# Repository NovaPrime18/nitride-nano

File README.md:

# nitride-nano

**Pocket-sized GaN buck/boost converter with USB-C PD input**

<table><tr>
<td></td>
<td></td>
</tr></table>

---

## Overview

Nitride-nano is an open-source, high-power-density buck/boost converter crammed into the smallest footprint possible. It targets the same use case as the [Miniware MDP-XP](https://www.miniware.com.cn/product/mdp-xp-digital-power-supply/)  a portable, wide-range programmable power supply. With a focus on **higher power density and a wider voltage range** rather than output ripple performance.

Built around EPC GaN FETs switching at up to 1 MHz and an LT8390A-based controller topology, it accepts either USB-C Power Delivery or high-voltage DC input and delivers up to 240 W from an XT90 output connector.

---

## Specifications

| Parameter | Value |
|---|---|
| Input voltage | 12 – 48 V |
| Output voltage | 0 – 60 V |
| Input / Output current | 20 A |
| Max output power | 240 W |
| Switching frequency | 1 MHz  |
| Topology | Non-inverting buck/boost |
| Input | XT90 / USB-C |
| Output | XT90 |
---

## USB-C Power Delivery

Nitride-nano negotiates full USB-C PD on the input side:

- **Fixed PDO** — standard 5/9/12/15/20 V profiles
- **PPS** — 5–21 V programmable (50 mV steps)
- **AVS / EPR** — 15–48 V extended power range

---

## Hardware

| Component | Part |
|---|---|
| MCU | STM32G474CEUx |
| Power stage FETs | EPC2367 (eGaN) |
| Controller | LT8390A / EVAL-LT8390A-AZ topology |
| Power monitor | INA228 (I²C, 16-bit) |
| Display | SSD1306 0.96″ OLED |
| UI | 3-button interface |

---

## Firmware

- STM32G474 HAL / bare-metal Rust
- SSD1306 OLED UI with 3-button navigation
- USB-C PD stack (Fixed / PPS / AVS negotiation) over I²C
- **Auto-tracking PD** — derives the input rail from the requested output voltage so the LT8390A stays in a clean buck or boost region instead of its lossier 4-switch band
- INA228 input/output power monitoring and real-time efficiency readout

---

## Thermal Sim
<table><tr>
<td></td>
<td></td>
</tr></table>

Simulated with Freecad, the enclosure reaches about 38 Degrees C (with a fan) when there's 10W of losses directly going into the heatsink from the GaNFETs. Real world performance is likely better, due to not all 10W leaving the Fets through the top.

---

## Testing — Revision 1 (1 MHz)

Bench results from Revision 1 hardware, measured at the operating points below.

| # | Input | Output | Efficiency |
|---|---|---|---|
| 1 | 25 V, 7 A — 174.2 W in | 36.6 V, 4.48 A — 164 W out | 94.1 % |
| 2 | 40 V, 3.61 A — 144.3 W in | 37.1 V, 3.48 A — 129.1 W out | 89.5 % |
| 3 | 13 V, 9.28 A — 120.6 W in | 36.5 V, 3 A — 109.1 W out | 90.5 % |

**Equipment:** Riden RD6024 bench supply (input) · EA-EL 3160-60 electronic load (output)

**Thermals:** the inductor core ran hottest at ~90 °C — by far the lossiest component on the board. The GaN FETs barely got above 60 °C.

---

## Testing — Revision 2 (2.2 µH, 1 MHz)

Bench results from Revision 2 hardware with the 2.2 µH Coilcraft XAL1010-222MED
inductor at 1 MHz switching. Efficiency is `Pout / Pin`.

### USB-C input

| # | Input | Output | Efficiency |
|---|---|---|---|
| 1 | 28 V, 3.957 A — 110.8 W in | 12.4 V, 8.04 A — 99.7 W out | 90.0 % |
| 2 | 36 V, 2.288 A — 82.4 W in | 12.4 V, 6.09 A — 75.5 W out | 91.7 % |
| 3 | 20 V, 4.75 A — 95.0 W in | 6.4 V, 12.92 A — 82.7 W out | 87.0 % |

### XT90 input

| # | Input | Output | Efficiency |
|---|---|---|---|
| 1 | 16 V, 10.54 A — 168.6 W in | 52 V, 2.97 A — 154.4 W out | 91.6 % |
| 2 | 13.81 V, 12.71 A — 175.5 W in | 38.6 V, 4 A — 154.4 W out | 88.0 % |
| 3 | 16 V, 14.13 A — 226.1 W in | 51.7 V, 4 A — 206.8 W out | 91.5 % |
| 4 | 16 V, 14.86 A — 237.8 W in | 51.8 V, 4.2 A — 217.6 W out | 91.5 % |
| 5 | 14 V, 17.2 A — 240.8 W in | 51.7 V, 4.2 A — 217.1 W out | 90.2 % |
| 6 | 24 V, 9.72 A — 233.3 W in | 52 V, 4.18 A — 217.4 W out | 93.2 % |
| 7 | 36 V, 6.42 A — 231.1 W in | 52.4 V, 4.18 A — 219.0 W out | 94.8 % |

**Peak efficiency:** 94.8 % at 36 V in → 52.4 V, 4.18 A (219.0 W out). The
highest input-power point was 240.8 W (14 V, 17.2 A) at 90.2 %; peak output
power was 219.0 W, up from 164 W on Revision 1.

---

## Acknowledgements / Based On

- [**PD240W** by theohg](https://github.com/theohg/PD240W) — USB-C PD input stage reference
- [**EVAL-LT8390A-AZ** by Analog Devices](https://www.analog.com/en/resources/evaluation-hardware-and-software/evaluation-boards-kits/eval-lt8390a-az.html) — buck/boost power stage reference

---

## License

Hardware design files are licensed under the **CERN Open Hardware Licence Version 2 – Strongly Reciprocal (CERN-OHL-S v2.0)**.

See [`LICENSE`](./LICENSE) for the full text, or visit [ohwr.org/cern_ohl_s_v2](https://ohwr.org/cern_ohl_s_v2.txt).

> In short: you are free to use, study, modify, and distribute this design, provided that any derivatives are released under the same licence and source files are made available.

---

## Status

> 🚧 Work in progress — Revision 1 and Revision 2 built and power-tested (results above).

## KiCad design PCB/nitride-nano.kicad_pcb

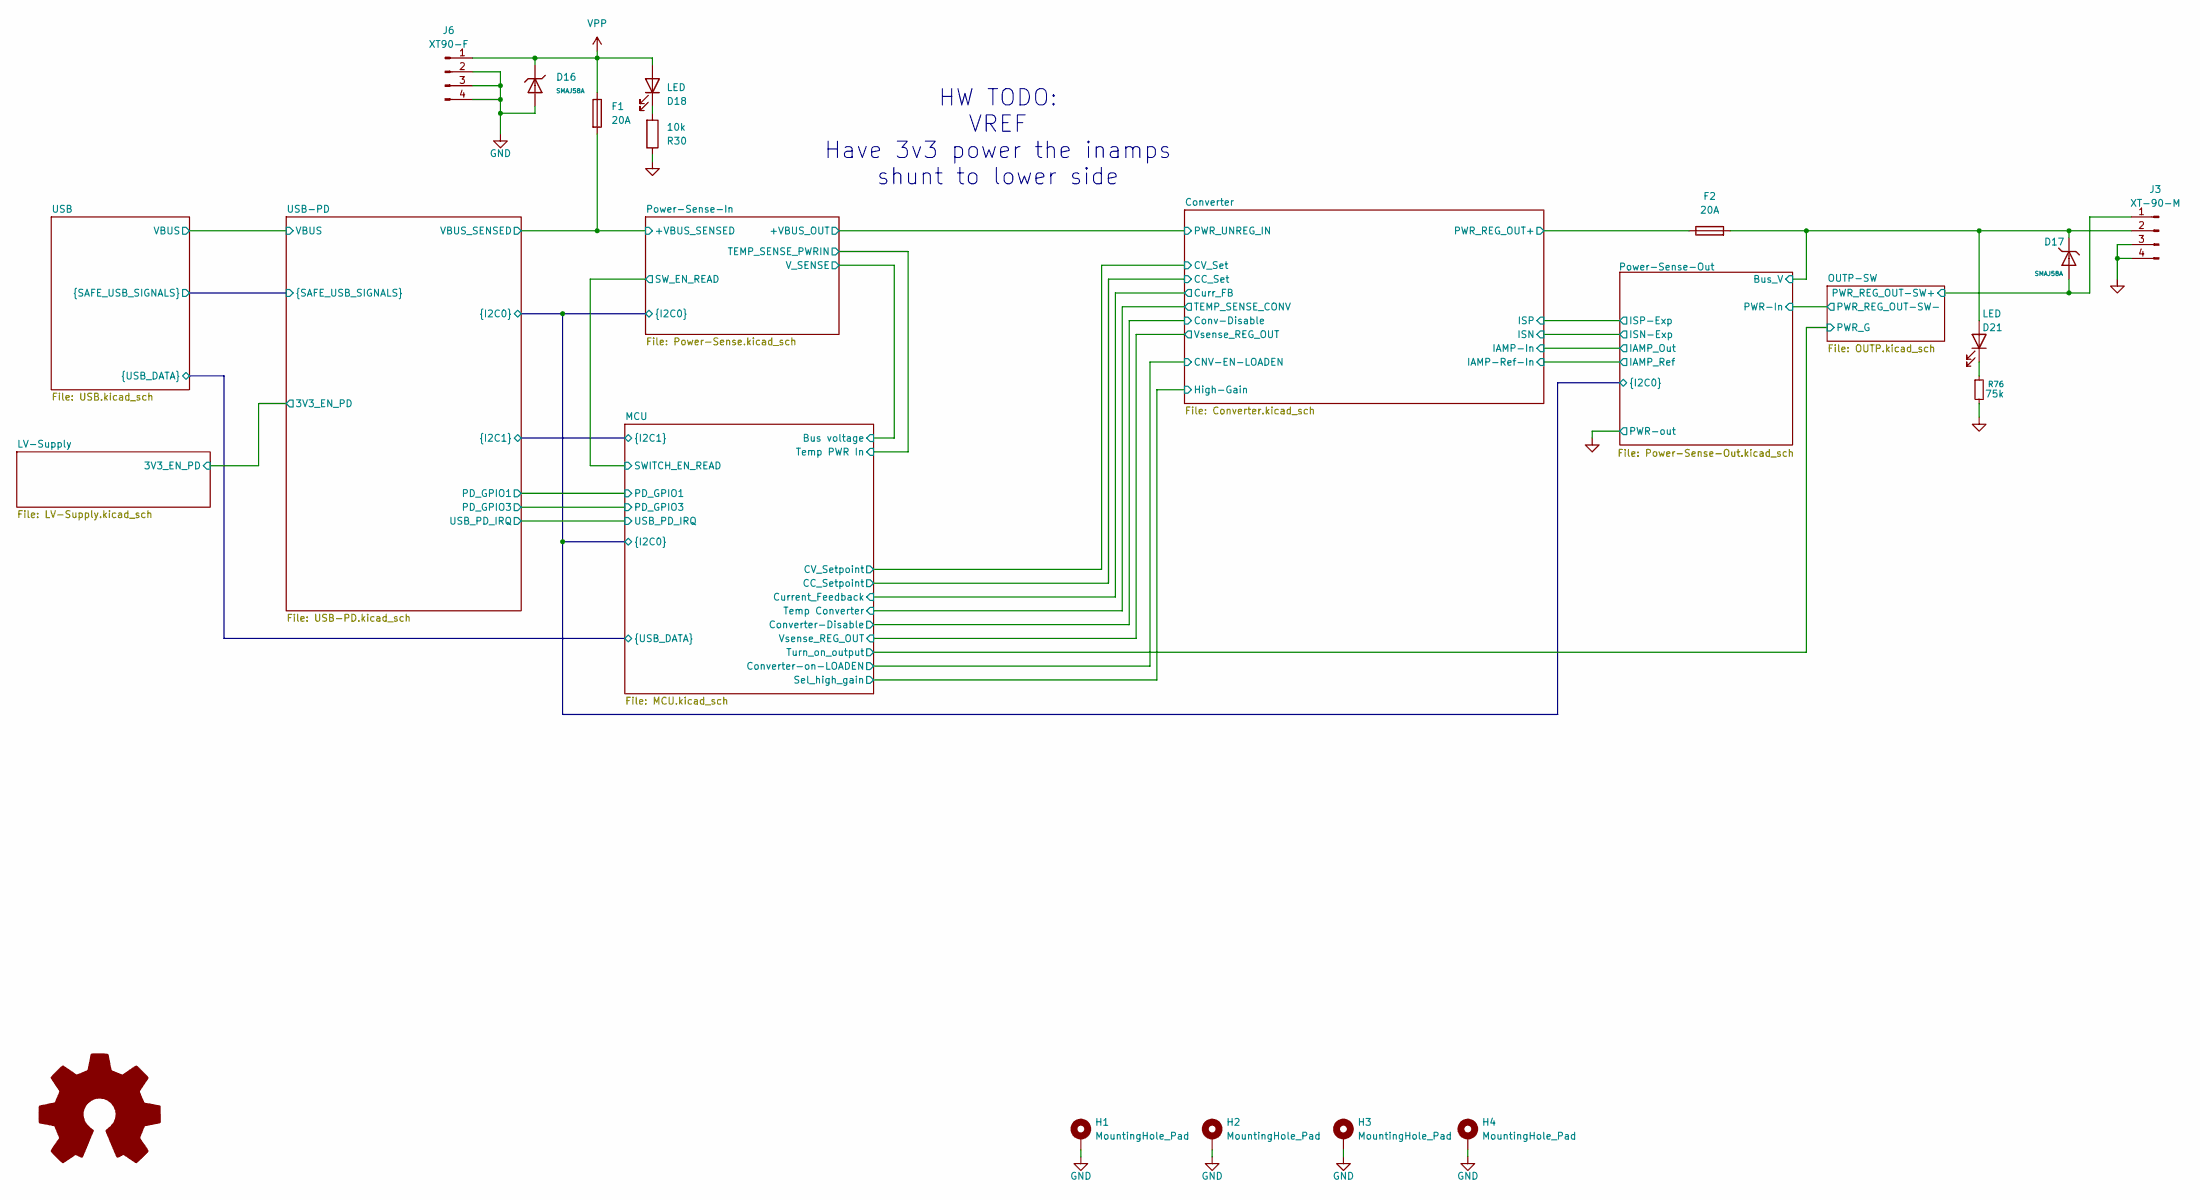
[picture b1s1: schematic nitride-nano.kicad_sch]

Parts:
D16, D17: SMAJ58A; D_SMA; Part SMAJ58A; LCSC C19077554
D18, D21: LED; LED_0603_1608Metric; LCSC C2286
F1, F2: 20A; Fuse_2512_6332Metric; LCSC C49269483
H1, H2, H3, H4: MountingHole_Pad; MountingHole_3.2mm_M3_Pad_Via
J3: XT-90-M; CONN-TH_XT90PW-M.G.Y; JLC C3040689
J6: XT90-F; CONN-TH_XT90PW-M; JLC C3040690
R30: 10k; R_0402_1005Metric; LCSC C2906861
R76: 75k; R_0402_1005Metric; LCSC C25798

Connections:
/Converter/PWR_REG_OUT+: F2.1; also elsewhere on the board
/OUTP-SW/PWR_REG_OUT-SW+: D17.2, J3.1; also elsewhere on the board
/Power-Sense-In/+VBUS_SENSED: F1.2; also elsewhere on the board
/Power-Sense-Out/Bus_V: D17.1, D21.2 (A), F2.2, J3.2; also elsewhere on the board
unnamed: D18.1 (K), R30.2
unnamed: D21.1 (K), R76.1
VPP: D16.1, D18.2 (A), F1.1, J6.1; also elsewhere on the board

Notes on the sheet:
HW TODO: VREF Have 3v3 power the inamps shunt to lower side

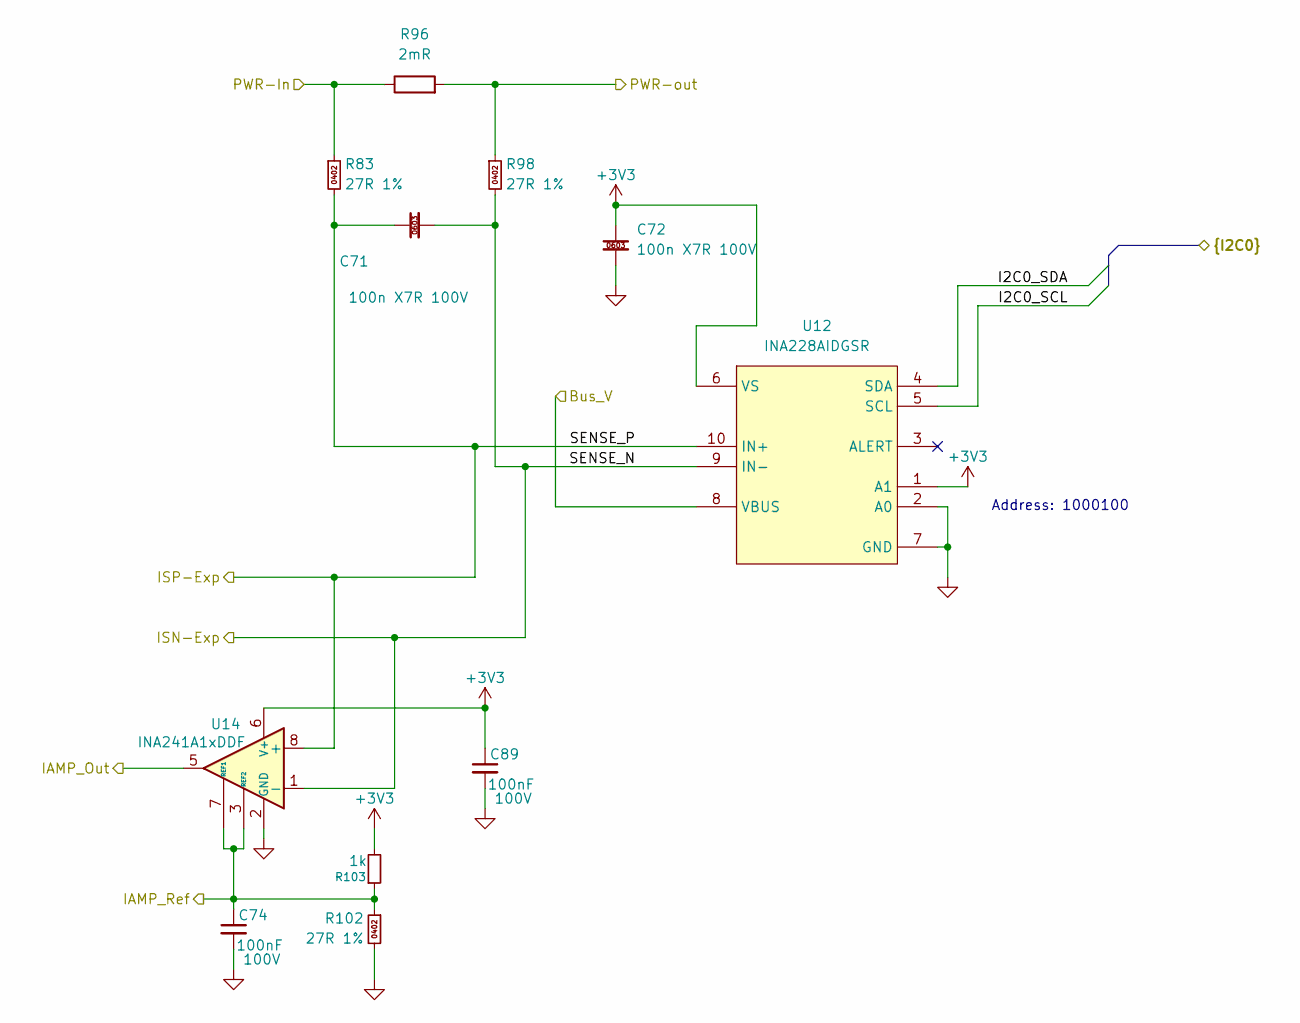
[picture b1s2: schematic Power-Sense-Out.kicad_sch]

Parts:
C71, C72: 100n X7R 100V; C_0603_1608Metric; Manufacturer Part Number CL10B104KC8NNNC; LCSC C15725
C74, C89: 100nF; C_0402_1005Metric; Voltage 100V; LCSC C162178
R83, R98, R102: 27R 1%; R_0402_1005Metric; Manufacturer Part Number RC0402FR-0727RL; LCSC C138021
R96: 2mR; R_2512_6332Metric; JLC C41382683
R103: 1k; R_0402_1005Metric; LCSC C106235
U12: INA228AIDGSR; vssop10_50p_300x300x110_mfg; Manufacturer Part Number INA228AIDGSR; LCSC C2887910
U14: INA241A1xDDF; SOT-23-8

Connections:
+3V3: C72.1, C89.1, R103.2, U12.1 (A1), U12.6 (VS), U14.6 (V+); also elsewhere on the board
/Converter/IAMP-In: U14.5; also elsewhere on the board
/Converter/IAMP-Ref-In: C74.1, R102.1, R103.1, U14.3 (REF2), U14.7 (REF1); also elsewhere on the board
/MCU/I2C0_SCL: U12.5 (SCL); also elsewhere on the board
/MCU/I2C0_SDA: U12.4 (SDA); also elsewhere on the board
/Power-Sense-Out/Bus_V: U12.8 (VBUS); also elsewhere on the board
/Power-Sense-Out/SENSE_N: C71.2, R98.2, U12.9 (IN-), U14.1 (-); also elsewhere on the board

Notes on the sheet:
Address: 1000100

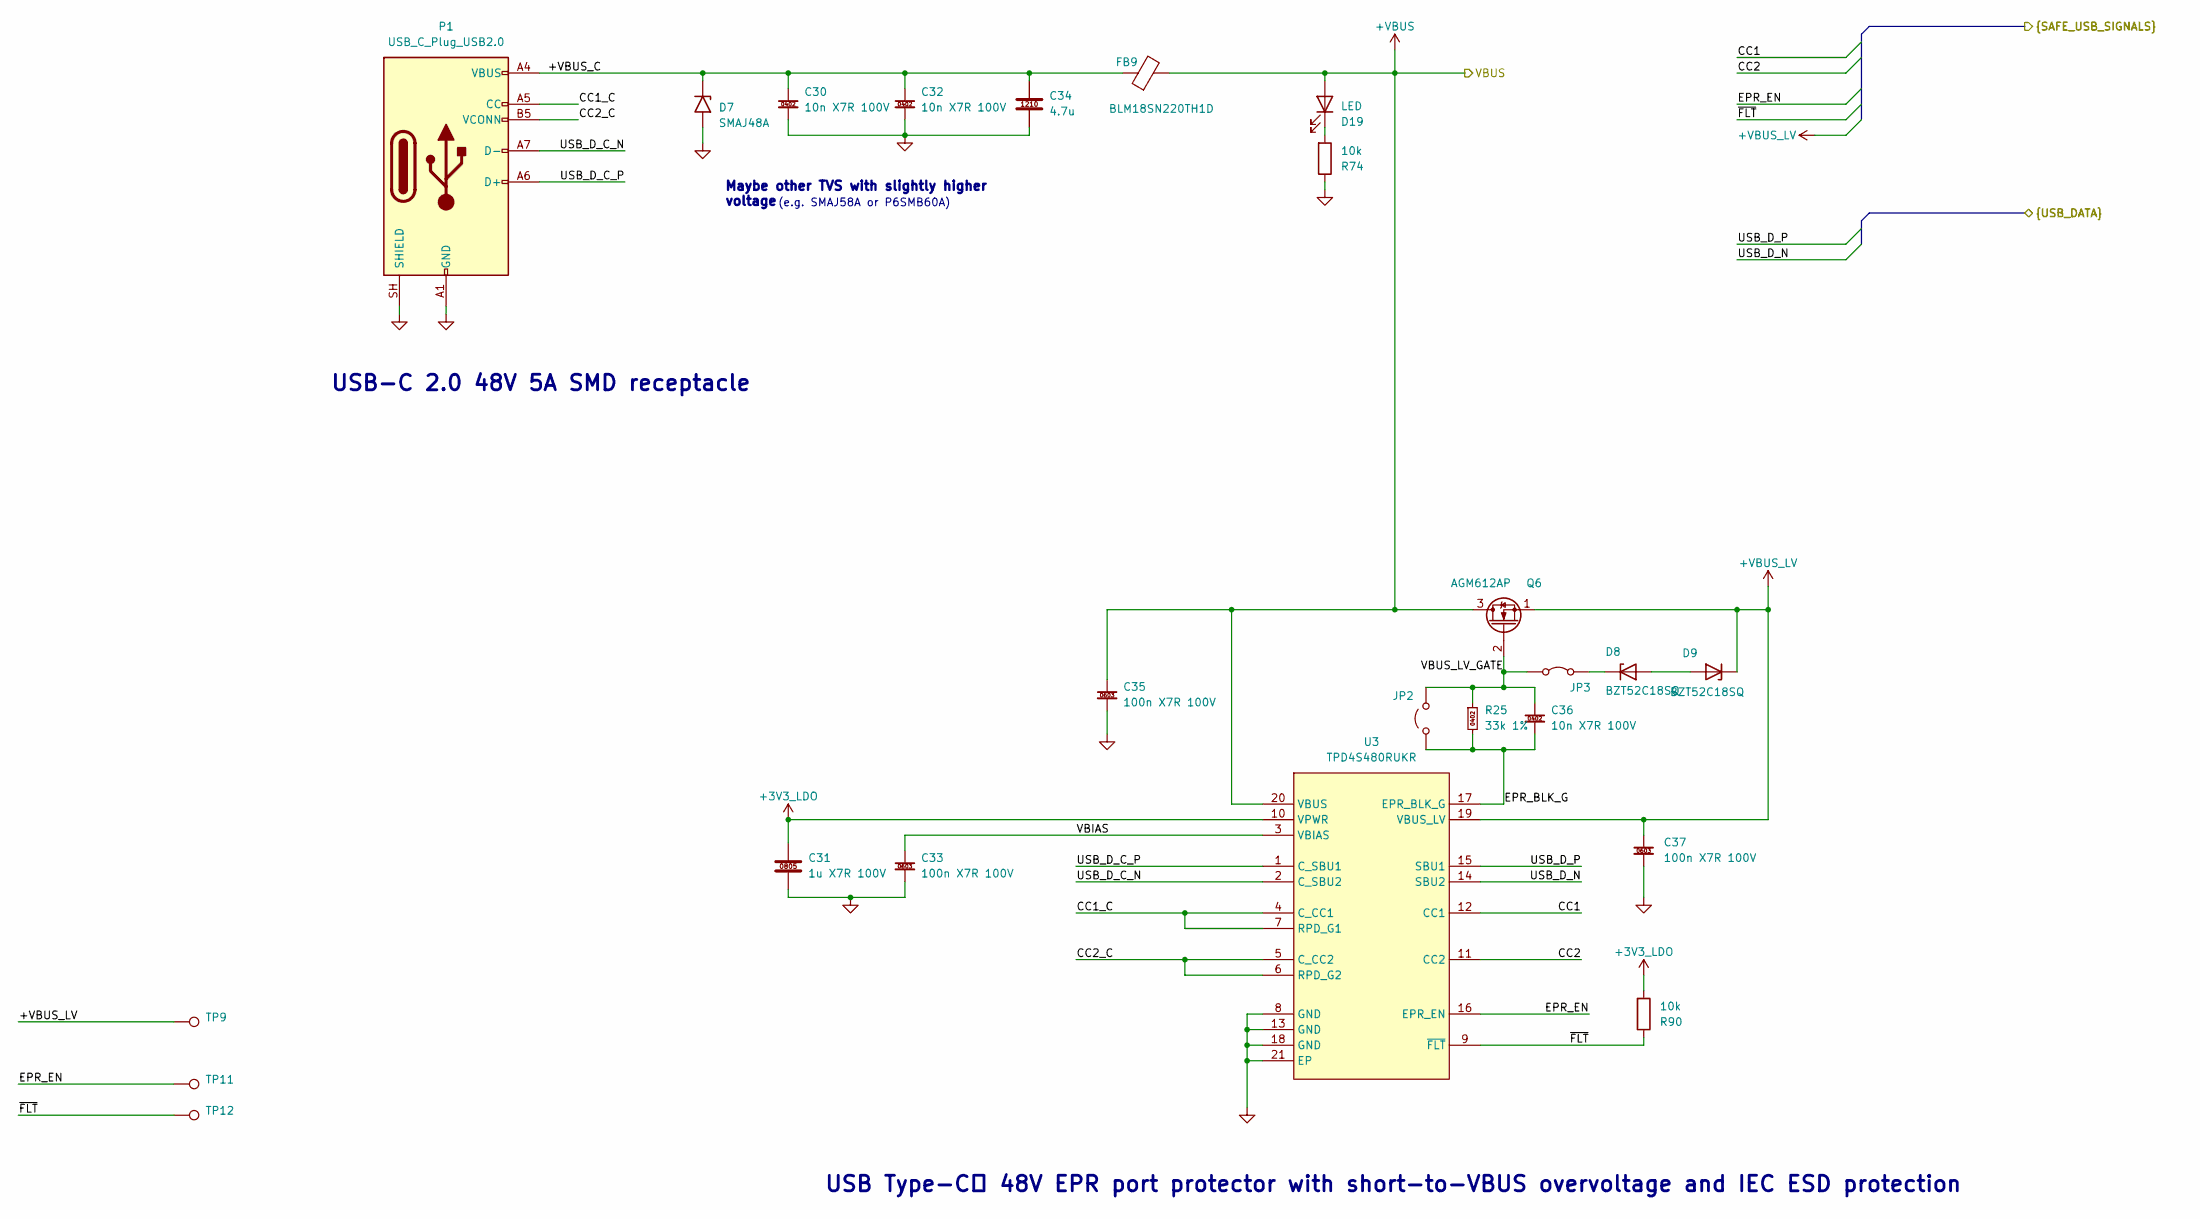
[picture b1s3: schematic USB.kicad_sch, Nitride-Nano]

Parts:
C30, C32, C36: 10n X7R 100V; C_0402_1005Metric; Manufacturer Part Number CC0402KRX7R0BB103; LCSC C527014
C31: 1u X7R 100V; C_0805_2012Metric; Manufacturer Part Number CC0805KKX7R0BB105; LCSC C5370002
C33, C35, C37: 100n X7R 100V; C_0603_1608Metric; Manufacturer Part Number CL10B104KC8NNNC; LCSC C15725
C34: 4.7u; C_1210_3225Metric; Manufacturer Part Number GCM32DC72A475KE02; LCSC C913445
D7: SMAJ48A; do-214ac_440p_430x250x230_n_p; Manufacturer Part Number SMAJ48A; LCSC C41376401
D8, D9: BZT52C18SQ; sod-323_230p_170x125x100_n; Manufacturer Part Number BZT52C18SQ; LCSC C2857090
D19: LED; LED_0603_1608Metric; LCSC C2286
FB9: BLM18SN220TH1D; fer_1608_09_n; Manufacturer Part Number BLM18SN220TH1D; LCSC C710392
JP2: jumper_solder_2pad_no; SolderJumper-2_P1.3mm_Open_RoundedPad1.0x1.5mm
JP3: jumper_solder_2pad_nc_kicad; SolderJumper-2_P1.3mm_Bridged2Bar_RoundedPad1.0x1.5mm
P1: USB_C_Plug_USB2.0; USB_C_Receptacle_GCT_USB4105-xx-A_16P_TopMnt_Horizontal; JLC C3025063
Q6: AGM612AP; vsonp8_65p_330x330x80_mfg; Manufacturer Part Number AGM612AP; LCSC C5349119
R25: 33k 1%; R_0402_1005Metric; Manufacturer Part Number RC0402FR-0733KL; LCSC C138003
R74, R90: 10k; R_0402_1005Metric; LCSC C2906861
TP9, TP11, TP12: tp_round_70; TestPoint_Pad_D1.0mm
U3: TPD4S480RUKR; wqfn20_40p_300x300x80_tp_170x170_n; Manufacturer Part Number TPD4S480RUKR; LCSC C43131250

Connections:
+3V3_LDO: C31.1, R90.2, U3.10 (VPWR); also elsewhere on the board
+VBUS: C35.1, D19.2 (A), FB9.2, Q6.3 (D), U3.20 (VBUS); also elsewhere on the board
+VBUS_LV: C37.1, D9.1 (K), Q6.1 (S), TP9.1 (1_1), U3.19 (VBUS_LV); also elsewhere on the board
/MCU/USB_D_N: U3.14 (SBU2); also elsewhere on the board
/MCU/USB_D_P: U3.15 (SBU1); also elsewhere on the board
/USB-PD/CC1: U3.12 (CC1); also elsewhere on the board
/USB-PD/CC2: U3.11 (CC2); also elsewhere on the board
/USB-PD/EPR_EN: TP11.1 (1_1), U3.16 (EPR_EN); also elsewhere on the board
/USB-PD/~FLT: R90.1, TP12.1 (1_1), U3.9 (~FLT); also elsewhere on the board
/USB/+VBUS_C: C30.1, C32.1, C34.1, D7.1 (A1), FB9.1, P1.A4 (VBUS), P1.A9 (VBUS), P1.B4 (VBUS), P1.B9 (VBUS)
/USB/CC1_C: P1.A5 (CC), U3.4 (C_CC1), U3.7 (RPD_G1)
/USB/CC2_C: P1.B5 (VCONN), U3.5 (C_CC2), U3.6 (RPD_G2)
/USB/EPR_BLK_G: C36.2, JP2.1 (A), R25.2, U3.17 (EPR_BLK_G)
/USB/USB_D_C_N: P1.A7 (D-), U3.2 (C_SBU2)
/USB/USB_D_C_P: P1.A6 (D+), U3.1 (C_SBU1)
/USB/VBIAS: C33.1, U3.3 (VBIAS)
/USB/VBUS_LV_GATE: C36.1, JP2.2 (B), JP3.1 (A), Q6.2 (G), R25.1
unnamed: D8.2 (A), D9.2 (A)
unnamed: D8.1 (K), JP3.2 (B)
unnamed: D19.1 (K), R74.2

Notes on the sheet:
USB Type-C™ 48V EPR port protector with short-to-VBUS overvoltage and IEC ESD protection
(e.g. SMAJ58A or P6SMB60A)
USB-C 2.0 48V 5A SMD receptacle
Maybe other TVS with slightly higher voltage

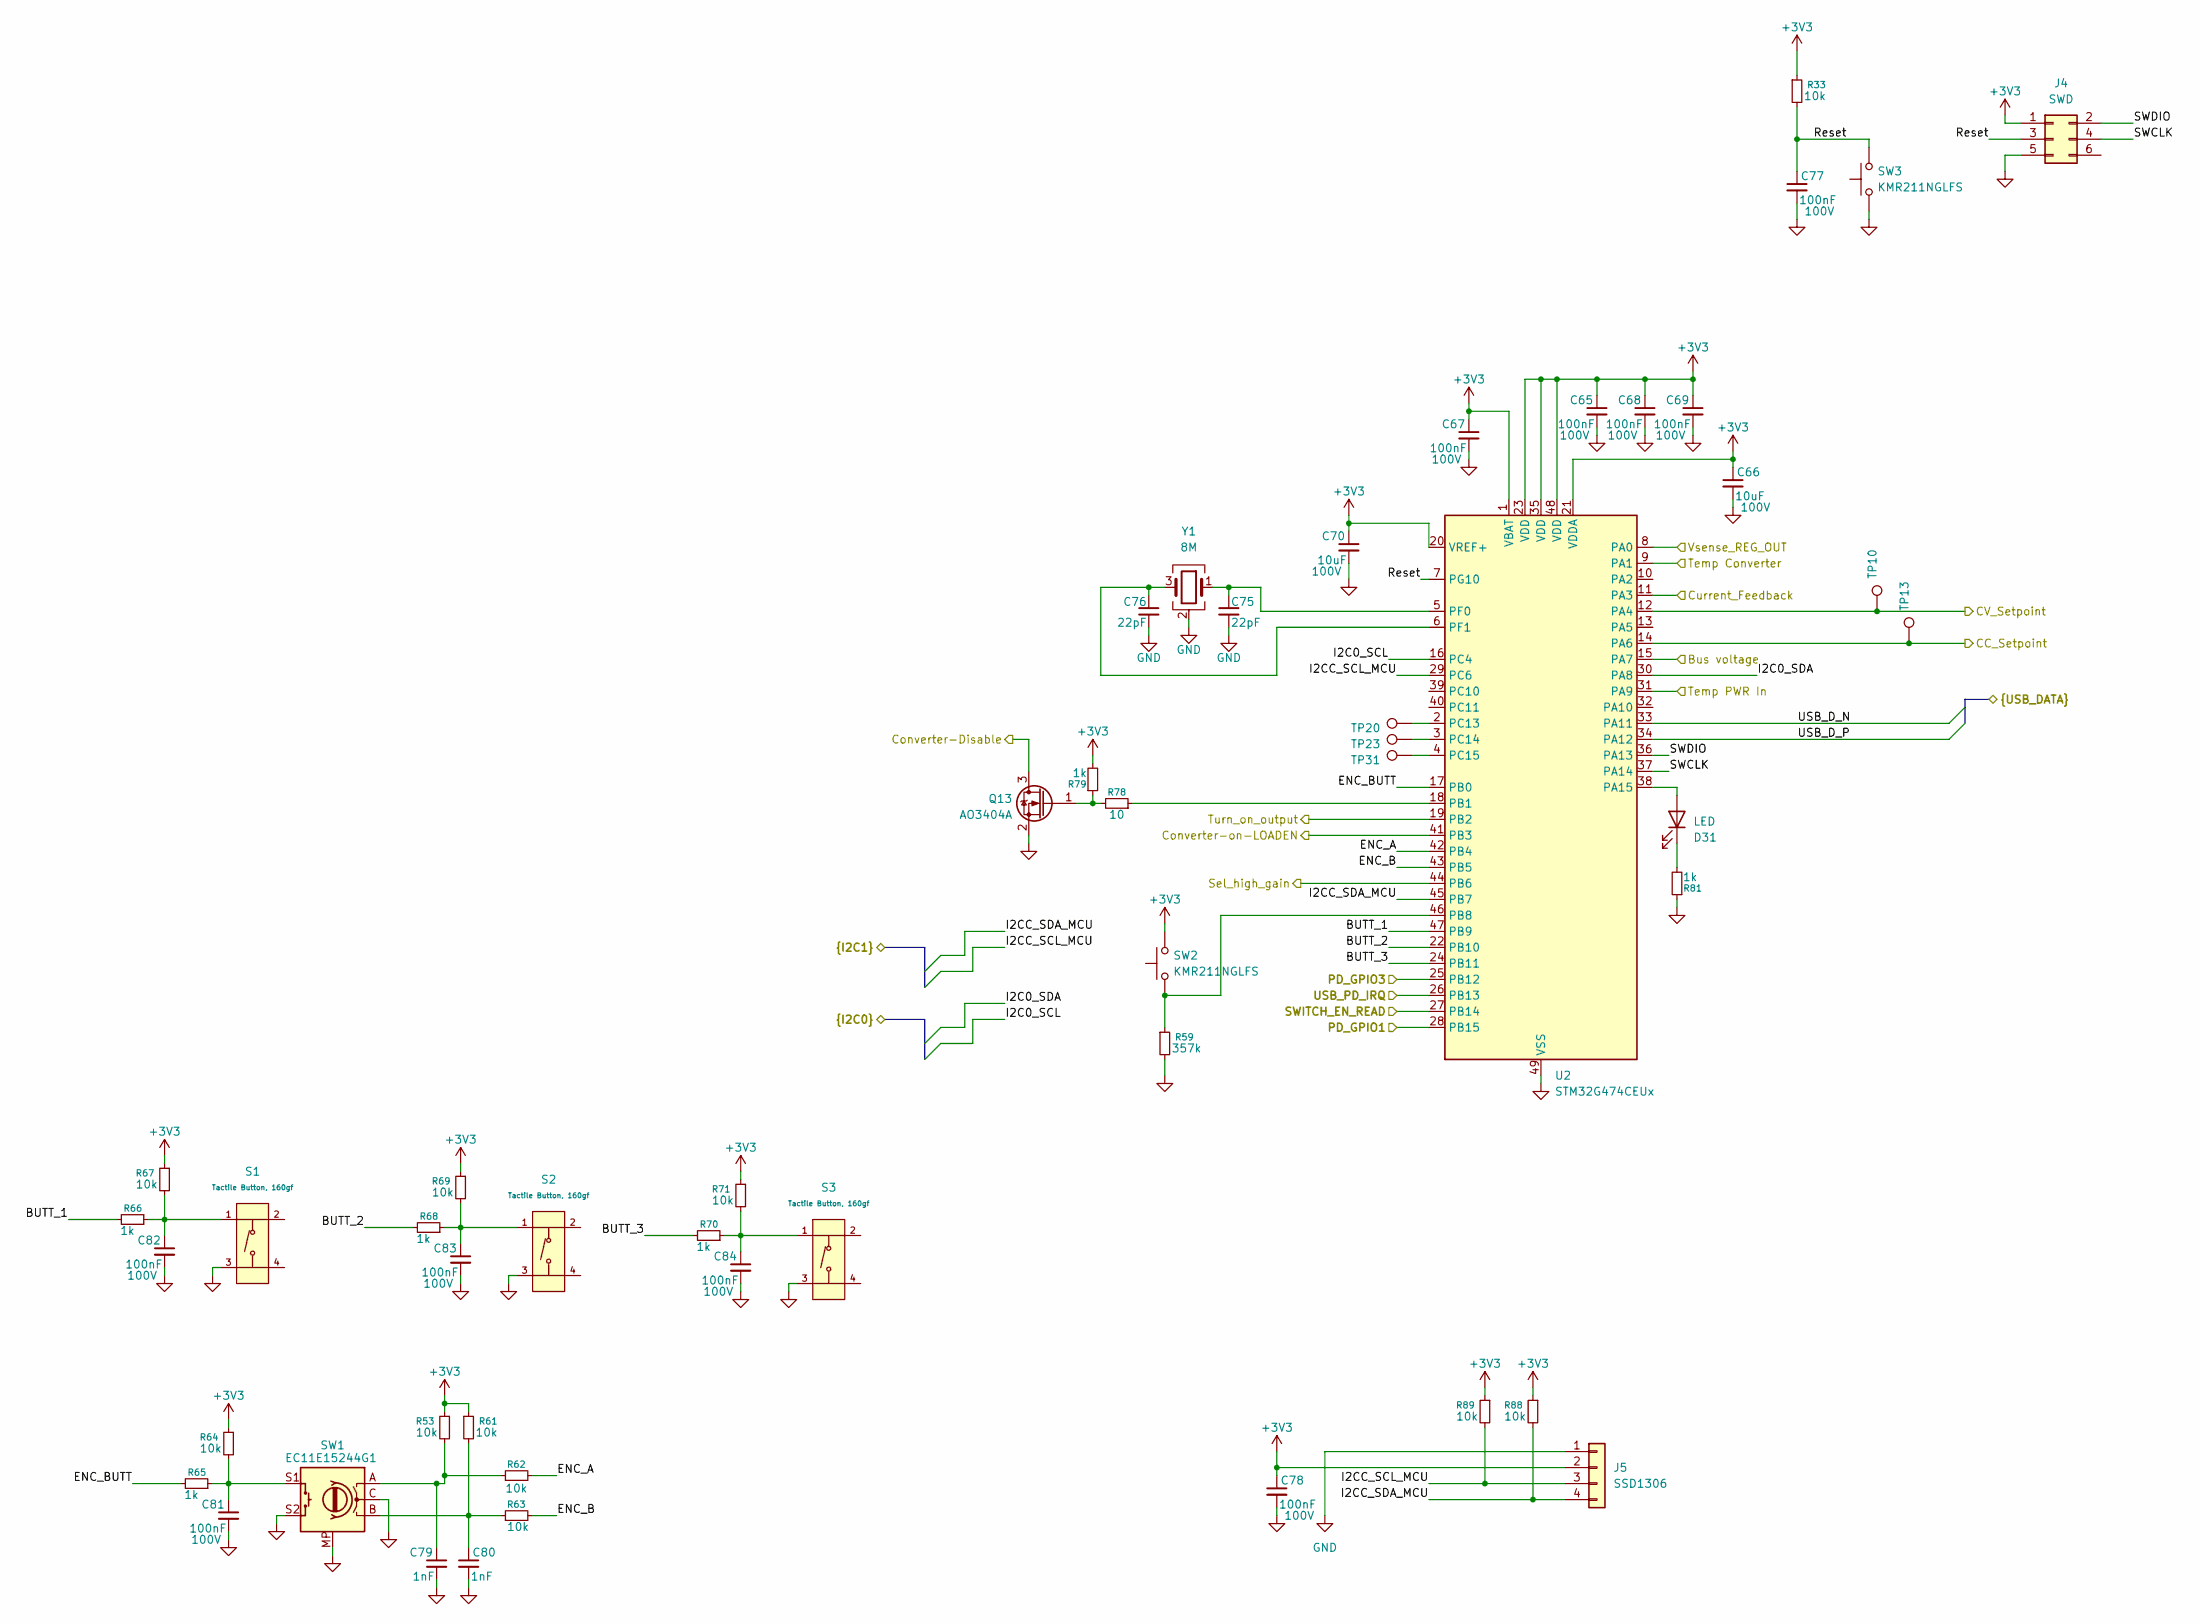
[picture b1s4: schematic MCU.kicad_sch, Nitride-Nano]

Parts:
C65, C67, C68, C69, C77, C78, C81, C82, C83, C84: 100nF; C_0402_1005Metric; Voltage 100V; LCSC C162178
C66, C70: 10uF; C_1210_3225Metric; Voltage 100V; LCSC C5156756
C75, C76: 22pF; C_0603_1608Metric; LCSC C1653
C79, C80: 1nF; C_0402_1005Metric; Voltage 50V; LCSC C1523
D31: LED; LED_0603_1608Metric; LCSC C2286
J4: SWD; Tag-Connect_TC2030-IDC-NL_2x03_P1.27mm_Vertical
J5: SSD1306; ssd13062
Q13: AO3404A; sot-23-3L_103p_300x130x110_n; Manufacturer Part Number AO3404A; LCSC C30010
R33, R53, R61, R62, R63, R64, R67, R69, R71, R88, R89: 10k; R_0402_1005Metric; LCSC C2906861
R59: 357k; R_0402_1005Metric; LCSC C27005
R65, R66, R68, R70, R79, R81: 1k; R_0402_1005Metric; LCSC C106235
R78: 10; R_0402_1005Metric; LCSC C25077
S1, S2, S3: Tactile Button, 160gf; SW-SMD_4P-L5.1-W5.1-P3.70-LS6.5-TL-2; Voltage Rating (Dc) 12V; Part TS-1187A-B-A-B; LCSC C318884
SW1: EC11E15244G1; RotaryEncoder_Alps_EC11E-Switch_Vertical_H20mm; JLC C370970
SW2, SW3: KMR211NGLFS; SW_Push_1P1T_NO_CK_KMR2; JLC C221676
TP10, TP13, TP20, TP23, TP31: tp_round_70; TestPoint_Pad_D1.0mm
U2: STM32G474CEUx; QFN-48-1EP_7x7mm_P0.5mm_EP5.6x5.6mm; JLC C1235412
Y1: 8M; Crystal_SMD_3225-4Pin_3.2x2.5mm; JLC C2682775

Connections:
+3V3: C65.1, C66.1, C67.1, C68.1, C69.1, C70.1, C78.1, J4.1, J5.2, R33.1, R53.1, R61.1, R64.1, R67.1, R69.1, R71.1, R79.2, R88.1, R89.1, SW2.2, U2.1 (VBAT), U2.20 (VREF+), U2.21 (VDDA), U2.23 (VDD), U2.35 (VDD), U2.48 (VDD); also elsewhere on the board
/Converter/CC_Set: TP13.1 (1_1), U2.14 (PA6); also elsewhere on the board
/Converter/CNV-EN-LOADEN: U2.41 (PB3); also elsewhere on the board
/Converter/CV_Set: TP10.1 (1_1), U2.12 (PA4); also elsewhere on the board
/Converter/Conv-Disable: Q13.3 (D); also elsewhere on the board
/Converter/High-Gain: U2.44 (PB6); also elsewhere on the board
/Converter/ISMON: U2.11 (PA3); also elsewhere on the board
/Converter/TEMP_SENSE_CONV: U2.9 (PA1); also elsewhere on the board
/Converter/Vsense_REG_OUT: U2.8 (PA0); also elsewhere on the board
/MCU/BUTT_1: R66.2, U2.47 (PB9)
/MCU/BUTT_2: R68.2, U2.22 (PB10)
/MCU/BUTT_3: R70.2, U2.24 (PB11)
/MCU/Bus voltage: U2.15 (PA7); also elsewhere on the board
/MCU/ENC_A: R62.2, U2.42 (PB4)
/MCU/ENC_B: R63.2, U2.43 (PB5)
/MCU/ENC_BUTT: R65.2, U2.17 (PB0)
/MCU/I2C0_SCL: U2.16 (PC4); also elsewhere on the board
/MCU/I2C0_SDA: U2.30 (PA8); also elsewhere on the board
/MCU/I2CC_SCL_MCU: J5.3, R89.2, U2.29 (PC6); also elsewhere on the board
/MCU/I2CC_SDA_MCU: J5.4, R88.2, U2.45 (PB7); also elsewhere on the board
/MCU/Reset: C77.1, J4.3, R33.2, SW3.2, U2.7 (PG10)
/MCU/SWCLK: J4.4, U2.37 (PA14)
/MCU/SWDIO: J4.2, U2.36 (PA13)
/MCU/SWITCH_EN_READ: U2.27 (PB14)
/MCU/Temp PWR In: U2.31 (PA9); also elsewhere on the board
/MCU/Turn_on_output: U2.19 (PB2); also elsewhere on the board
/MCU/USB_D_N: U2.33 (PA11); also elsewhere on the board
/MCU/USB_D_P: U2.34 (PA12); also elsewhere on the board
/USB-PD/PD_GPIO1: U2.28 (PB15); also elsewhere on the board
/USB-PD/PD_GPIO3: U2.25 (PB12); also elsewhere on the board
/USB-PD/USB_PD_IRQ: U2.26 (PB13); also elsewhere on the board
unnamed: C79.1, R53.2, R62.1, SW1.A
unnamed: C80.1, R61.2, R63.1, SW1.B
unnamed: C81.1, R64.2, R65.1, SW1.S1
unnamed: D31.2 (A), U2.38 (PA15)
unnamed: Q13.1 (G), R78.2, R79.1
unnamed: C82.1, R66.1, R67.2, S1.1 (A)
unnamed: C83.1, R68.1, R69.2, S2.1 (A)
unnamed: C84.1, R70.1, R71.2, S3.1 (A)
unnamed: R78.1, U2.18 (PB1)
unnamed: R59.1, SW2.1, U2.46 (PB8)
unnamed: TP20.1 (1_1), U2.2 (PC13)
unnamed: TP23.1 (1_1), U2.3 (PC14)
unnamed: TP31.1 (1_1), U2.4 (PC15)
unnamed: C75.1, U2.5 (PF0), Y1.1
unnamed: C76.1, U2.6 (PF1), Y1.3

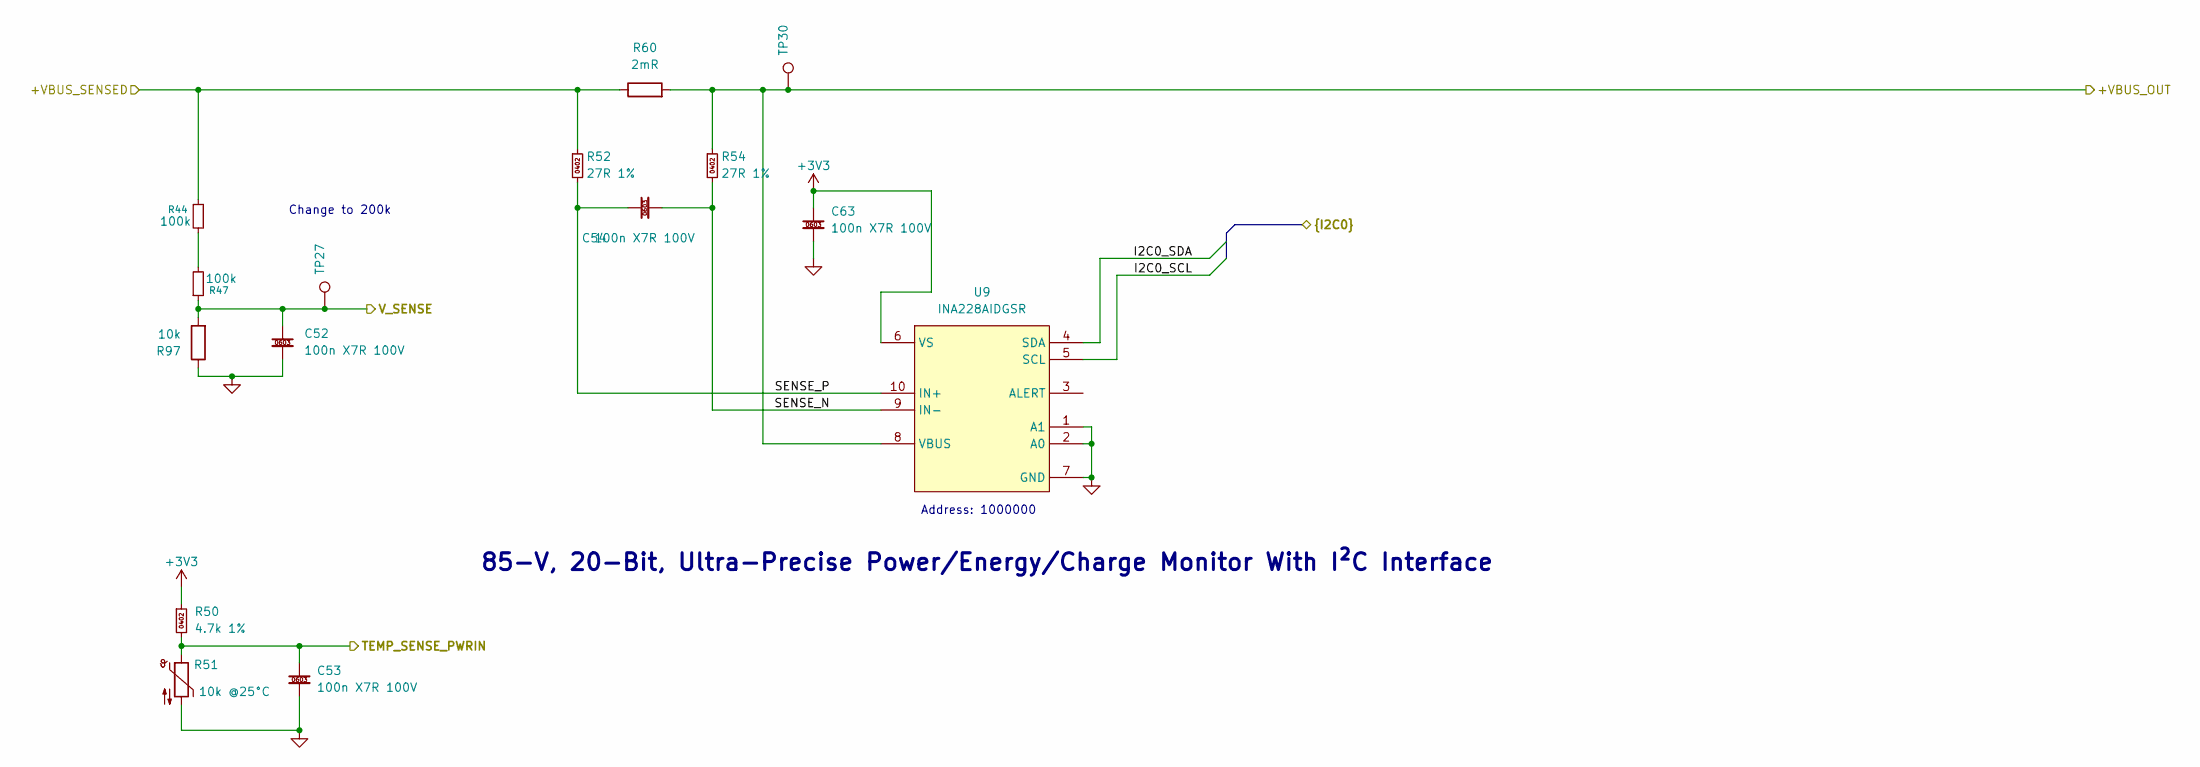
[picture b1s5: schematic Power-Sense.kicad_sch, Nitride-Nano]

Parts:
C52, C53, C54, C63: 100n X7R 100V; C_0603_1608Metric; Manufacturer Part Number CL10B104KC8NNNC; LCSC C15725
R44, R47: 100k; R_0402_1005Metric; LCSC C60491
R50: 4.7k 1%; R_0402_1005Metric; Manufacturer Part Number 0402WGF1003TCE; LCSC C105871
R51: 10k @25°C; R_0402_1005Metric; LCSC C77131
R52, R54: 27R 1%; R_0402_1005Metric; Manufacturer Part Number RC0402FR-0727RL; LCSC C138021
R60: 2mR; R_2512_6332Metric; JLC C41382683
R97: 10k; R_0402_1005Metric; LCSC C2906861
TP27, TP30: tp_round_70; TestPoint_Pad_D1.0mm
U9: INA228AIDGSR; vssop10_50p_300x300x110_mfg; Manufacturer Part Number INA228AIDGSR; LCSC C2887910

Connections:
+3V3: C63.1, R50.1, U9.6 (VS); also elsewhere on the board
/Converter/PWR_UNREG_IN: R54.1, R60.2, TP30.1 (1_1), U9.8 (VBUS); also elsewhere on the board
/MCU/Bus voltage: C52.1, R47.1, R97.2, TP27.1 (1_1); also elsewhere on the board
/MCU/I2C0_SCL: U9.5 (SCL); also elsewhere on the board
/MCU/I2C0_SDA: U9.4 (SDA); also elsewhere on the board
/MCU/Temp PWR In: C53.1, R50.2, R51.1; also elsewhere on the board
/Power-Sense-In/+VBUS_SENSED: R44.1, R52.1, R60.1; also elsewhere on the board
/Power-Sense-In/SENSE_N: C54.2, R54.2, U9.9 (IN-)
/Power-Sense-In/SENSE_P: C54.1, R52.2, U9.10 (IN+)
unnamed: R44.2, R47.2

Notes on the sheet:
85-V, 20-Bit, Ultra-Precise Power/Energy/Charge Monitor With I²C Interface
Address: 1000000
Change to 200k

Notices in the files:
README.md:
License: CERN-OHL-S v2.0
